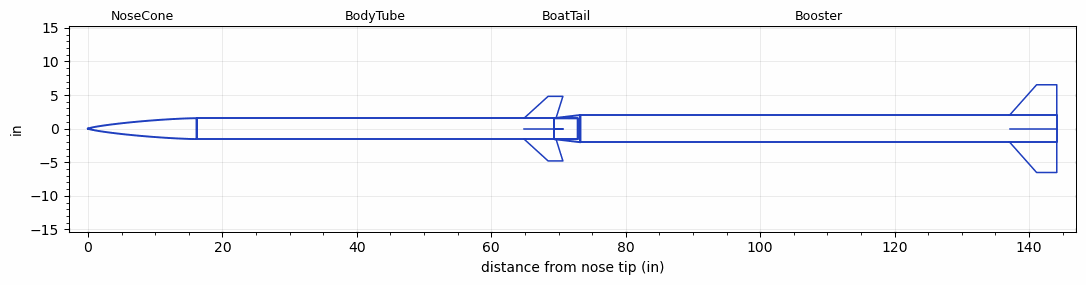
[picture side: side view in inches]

<RASAeroDocument>
 <FileVersion>2</FileVersion>
 <RocketDesign>
  <NoseCone>
   <Length>16.142</Length>
   <Diameter>3.11</Diameter>
   <Shape>Von Karman Ogive</Shape>
   <Location>0</Location>
  </NoseCone>
  <BodyTube>
   <Length>53.182</Length>
   <Diameter>3.11</Diameter>
   <Location>16.142</Location>
   <BoattailLength>3.543</BoattailLength>
   <BoattailRearDiameter>3.1</BoattailRearDiameter>
   <Overhang>0.3000002</Overhang>
   <Fin>
    <Count>4</Count>
    <Chord>4.75</Chord>
    <Span>3.25</Span>
    <SweepDistance>3.575</SweepDistance>
    <TipChord>2.2</TipChord>
    <Thickness>0.205</Thickness>
    <LERadius>0.01</LERadius>
    <Location>4.45</Location>
    <AirfoilSection>Hexagonal</AirfoilSection>
    <FX1>0.826</FX1>
    <FX3>0.826</FX3>
   </Fin>
   <Protuberance>
    <StreamlinedNoBaseDrag>0</StreamlinedNoBaseDrag>
    <StreamlinedWithBaseDrag>0</StreamlinedWithBaseDrag>
    <InclinedPlate1Angle>30</InclinedPlate1Angle>
    <InclinedPlate1FrontalArea>0.485</InclinedPlate1FrontalArea>
    <InclinedPlate2Angle>0</InclinedPlate2Angle>
    <InclinedPlate2FrontalArea>0</InclinedPlate2FrontalArea>
   </Protuberance>
  </BodyTube>
  <BoatTail>
   <Length>3.543</Length>
   <Diameter>3.11</Diameter>
   <RearDiameter>3.1</RearDiameter>
   <Location>69.324</Location>
  </BoatTail>
  <Booster>
   <Length>70.866</Length>
   <Diameter>4.055</Diameter>
   <InsideDiameter>3.11</InsideDiameter>
   <RailGuideDiameter>0.6</RailGuideDiameter>
   <RailGuideHeight>0.66</RailGuideHeight>
   <Location>69.324</Location>
   <ShoulderLength>3.937</ShoulderLength>
   <Fin>
    <Count>4</Count>
    <Chord>7</Chord>
    <Span>4.5</Span>
    <SweepDistance>4</SweepDistance>
    <TipChord>3</TipChord>
    <Thickness>0.205</Thickness>
    <LERadius>0.01</LERadius>
    <Location>7</Location>
    <AirfoilSection>Hexagonal</AirfoilSection>
    <FX1>1.063</FX1>
    <FX3>1.063</FX3>
   </Fin>
   <Protuberance>
    <StreamlinedNoBaseDrag>0</StreamlinedNoBaseDrag>
    <StreamlinedWithBaseDrag>0</StreamlinedWithBaseDrag>
    <InclinedPlate1Angle>30</InclinedPlate1Angle>
    <InclinedPlate1FrontalArea>0.485</InclinedPlate1FrontalArea>
    <InclinedPlate2Angle>0</InclinedPlate2Angle>
    <InclinedPlate2FrontalArea>0</InclinedPlate2FrontalArea>
   </Protuberance>
  </Booster>
  <Surface>Smooth Paint</Surface>
  <ModifiedBarrowman>False</ModifiedBarrowman>
  <Turbulence>True</Turbulence>
  <UseBooster1>False</UseBooster1>
  <UseBooster2>False</UseBooster2>
 </RocketDesign>
 <LaunchSite>
  <Altitude>2067</Altitude>
  <Pressure>28.74</Pressure>
  <RodAngle>0</RodAngle>
  <RodLength>20</RodLength>
  <Temperature>115</Temperature>
  <WindSpeed>12</WindSpeed>
 </LaunchSite>
 <Recovery>
  <Altitude1>1000</Altitude1>
  <Altitude2>1700</Altitude2>
  <DeviceType1>Parachute</DeviceType1>
  <DeviceType2>Parachute</DeviceType2>
  <Event1>True</Event1>
  <Event2>True</Event2>
  <Size1>9</Size1>
  <Size2>36</Size2>
  <EventType1>Apogee</EventType1>
  <EventType2>Altitude</EventType2>
  <CD1>1.75</CD1>
  <CD2>2.2</CD2>
 </Recovery>
 <SimulationList>
  <Simulation>
   <SustainerEngine>M2045-BS  (CTI)</SustainerEngine>
   <SustainerLaunchWt>20.7</SustainerLaunchWt>
   <SustainerNozzleDiameter>1.77</SustainerNozzleDiameter>
   <SustainerCG>45.71</SustainerCG>
   <SustainerIgnitionDelay>15</SustainerIgnitionDelay>
   <Booster1Engine>O3800  (AMW)</Booster1Engine>
   <Booster1LaunchWt>64.4</Booster1LaunchWt>
   <Booster1SeparationDelay>0</Booster1SeparationDelay>
   <Booster1IgnitionDelay>0</Booster1IgnitionDelay>
   <Booster1CG>91.85</Booster1CG>
   <Booster1NozzleDiameter>2.32</Booster1NozzleDiameter>
   <IncludeBooster1>True</IncludeBooster1>
   <Booster2Delay>0</Booster2Delay>
   <IncludeBooster2>False</IncludeBooster2>
   <TimetoApogee>99.40171</TimetoApogee>
   <MaxAltitude>143887</MaxAltitude>
   <MaxVelocity>3902.002</MaxVelocity>
  </Simulation>
  <Simulation>
   <SustainerEngine>M2045-BS  (CTI)</SustainerEngine>
   <SustainerLaunchWt>21.2</SustainerLaunchWt>
   <SustainerNozzleDiameter>1.875</SustainerNozzleDiameter>
   <SustainerCG>45.53</SustainerCG>
   <SustainerIgnitionDelay>300</SustainerIgnitionDelay>
   <Booster1Engine>O3800  (AMW)</Booster1Engine>
   <Booster1LaunchWt>64.9</Booster1LaunchWt>
   <Booster1SeparationDelay>0</Booster1SeparationDelay>
   <Booster1IgnitionDelay>0</Booster1IgnitionDelay>
   <Booster1CG>91.69</Booster1CG>
   <Booster1NozzleDiameter>2.7</Booster1NozzleDiameter>
   <IncludeBooster1>True</IncludeBooster1>
   <Booster2Delay>0</Booster2Delay>
   <IncludeBooster2>False</IncludeBooster2>
   <TimetoApogee>42.38982</TimetoApogee>
   <MaxAltitude>33952.86</MaxAltitude>
   <MaxVelocity>2048.479</MaxVelocity>
  </Simulation>
  <Simulation>
   <SustainerEngine>M2045-BS  (CTI)</SustainerEngine>
   <SustainerLaunchWt>21.2</SustainerLaunchWt>
   <SustainerNozzleDiameter>1.875</SustainerNozzleDiameter>
   <SustainerCG>45.53</SustainerCG>
   <SustainerIgnitionDelay>1000</SustainerIgnitionDelay>
   <Booster1Engine>O3800  (AMW)</Booster1Engine>
   <Booster1LaunchWt>64.9</Booster1LaunchWt>
   <Booster1SeparationDelay>1000</Booster1SeparationDelay>
   <Booster1IgnitionDelay>0</Booster1IgnitionDelay>
   <Booster1CG>91.69</Booster1CG>
   <Booster1NozzleDiameter>2.7</Booster1NozzleDiameter>
   <IncludeBooster1>True</IncludeBooster1>
   <Booster2Delay>0</Booster2Delay>
   <IncludeBooster2>False</IncludeBooster2>
   <TimetoApogee>39.29941</TimetoApogee>
   <MaxAltitude>30233.69</MaxAltitude>
   <MaxVelocity>152.2425</MaxVelocity>
  </Simulation>
  <Simulation>
   <SustainerEngine>M2045-BS  (CTI)</SustainerEngine>
   <SustainerLaunchWt>20.7</SustainerLaunchWt>
   <SustainerNozzleDiameter>1.77</SustainerNozzleDiameter>
   <SustainerCG>45.71</SustainerCG>
   <SustainerIgnitionDelay>20</SustainerIgnitionDelay>
   <Booster1Engine>O3800MALFUNC  (AMW)</Booster1Engine>
   <Booster1LaunchWt>64.4</Booster1LaunchWt>
   <Booster1SeparationDelay>0</Booster1SeparationDelay>
   <Booster1IgnitionDelay>0</Booster1IgnitionDelay>
   <Booster1CG>91.85</Booster1CG>
   <Booster1NozzleDiameter>2.32</Booster1NozzleDiameter>
   <IncludeBooster1>True</IncludeBooster1>
   <Booster2Delay>0</Booster2Delay>
   <IncludeBooster2>False</IncludeBooster2>
   <TimetoApogee>86.57822</TimetoApogee>
   <MaxAltitude>80579.39</MaxAltitude>
   <MaxVelocity>3193.16</MaxVelocity>
  </Simulation>
 </SimulationList>
</RASAeroDocument>
